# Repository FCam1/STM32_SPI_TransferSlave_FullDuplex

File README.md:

## SPI_TransferSlave_FullDuplexMode

Communicate with an STM32 as slave in full duplex mode via SPI 

Tested to communicate with an Raspberry PI3

Made to be add in the SPI folder of this repositorie :  https://github.com/rogerclarkmelbourne/Arduino_STM32

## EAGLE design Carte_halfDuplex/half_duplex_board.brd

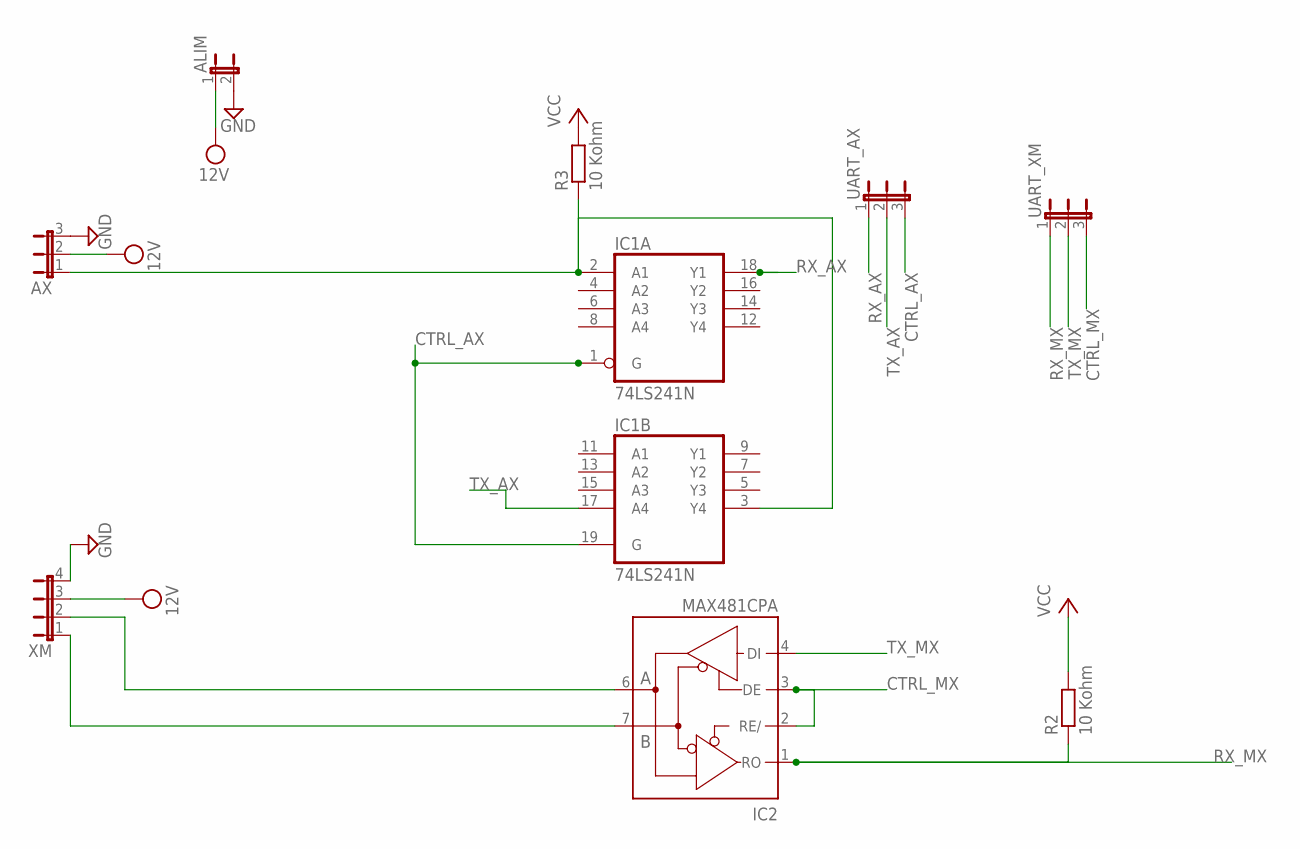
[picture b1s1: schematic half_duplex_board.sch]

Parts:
ALIM: JP1E; JP1
AX: JP2W
IC1: 74LS241N; DIL20
IC2: MAX481CPA; DIL08
R2, R3: 10 Kohm; 0207/10
UART_AX: JP2W
UART_XM: JP2W
XM: JP4E; JP4

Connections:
CTRL_AX: IC1.1 (G), IC1.19 (G)
CTRL_MX: IC2.2 (RE/), IC2.3 (DE), UART_XM.3
GND: ALIM.2, AX.3, IC1.10 (GND), IC2.5 (GND), XM.4
unnamed: IC2.7 (B), XM.1
unnamed: IC2.6 (A), XM.2
unnamed: AX.1, IC1.2 (A1), IC1.3 (Y4), R3.1
RX_AX: IC1.18 (Y1)
RX_MX: IC2.1 (RO), R2.1, UART_XM.1
TX_AX: IC1.17 (A4)
TX_MX: IC2.4 (DI), UART_XM.2
VCC: IC1.20 (VCC), IC2.8 (VCC), R2.2, R3.2
VDD: ALIM.1, AX.2, XM.3

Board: 2 copper layers, 9 parts (0 on the bottom side), 10 nets, no tracks yet.

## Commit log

2017-11-30 remove old files
2018-01-09 suppression carte half duplex
